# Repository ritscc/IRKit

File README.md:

# IRKit
KC3 2019 RCC勉強会
IRKit 基板設計データ
# Dependency
[KiCAD](http://kicad-pcb.org)

## FootPrint
- [ZX62-B-PA(33)](https://www.snapeda.com/parts/ZX62-B-5PA%2833%29/Hirose%20Electric%20Co%20Ltd/view-part/)
- [BS170](https://www.snapeda.com/parts/BS170/ON%20Semiconductor/view-part/)
- [kc3_logo](KiCad/lib/kc3-logo/kc3_logo.pretty)
- [AKI-PARTS](KiCad/lib/AKI-PARTS.pretty)

# Setup
1. `git clone git@github.com:ritscc/IRKit.git`
1. Log in [snapeda](https://www.snapeda.com/account/login/)
1. Download & unzip [ZX62-B-PA(33)](https://www.snapeda.com/parts/ZX62-B-5PA%2833%29/Hirose%20Electric%20Co%20Ltd/view-part/), [BS170](https://www.snapeda.com/parts/BS170/ON%20Semiconductor/view-part/) FootPront to IRKit project directory `./IRKit/`

# License
This software is released under the MIT License, see LICENSE.

# Authors
RCC
- aonori@[aonrjp](https://aonr.jp)
- nekopanda@[hirotta3a](https://twitter.com/hirotta3a)

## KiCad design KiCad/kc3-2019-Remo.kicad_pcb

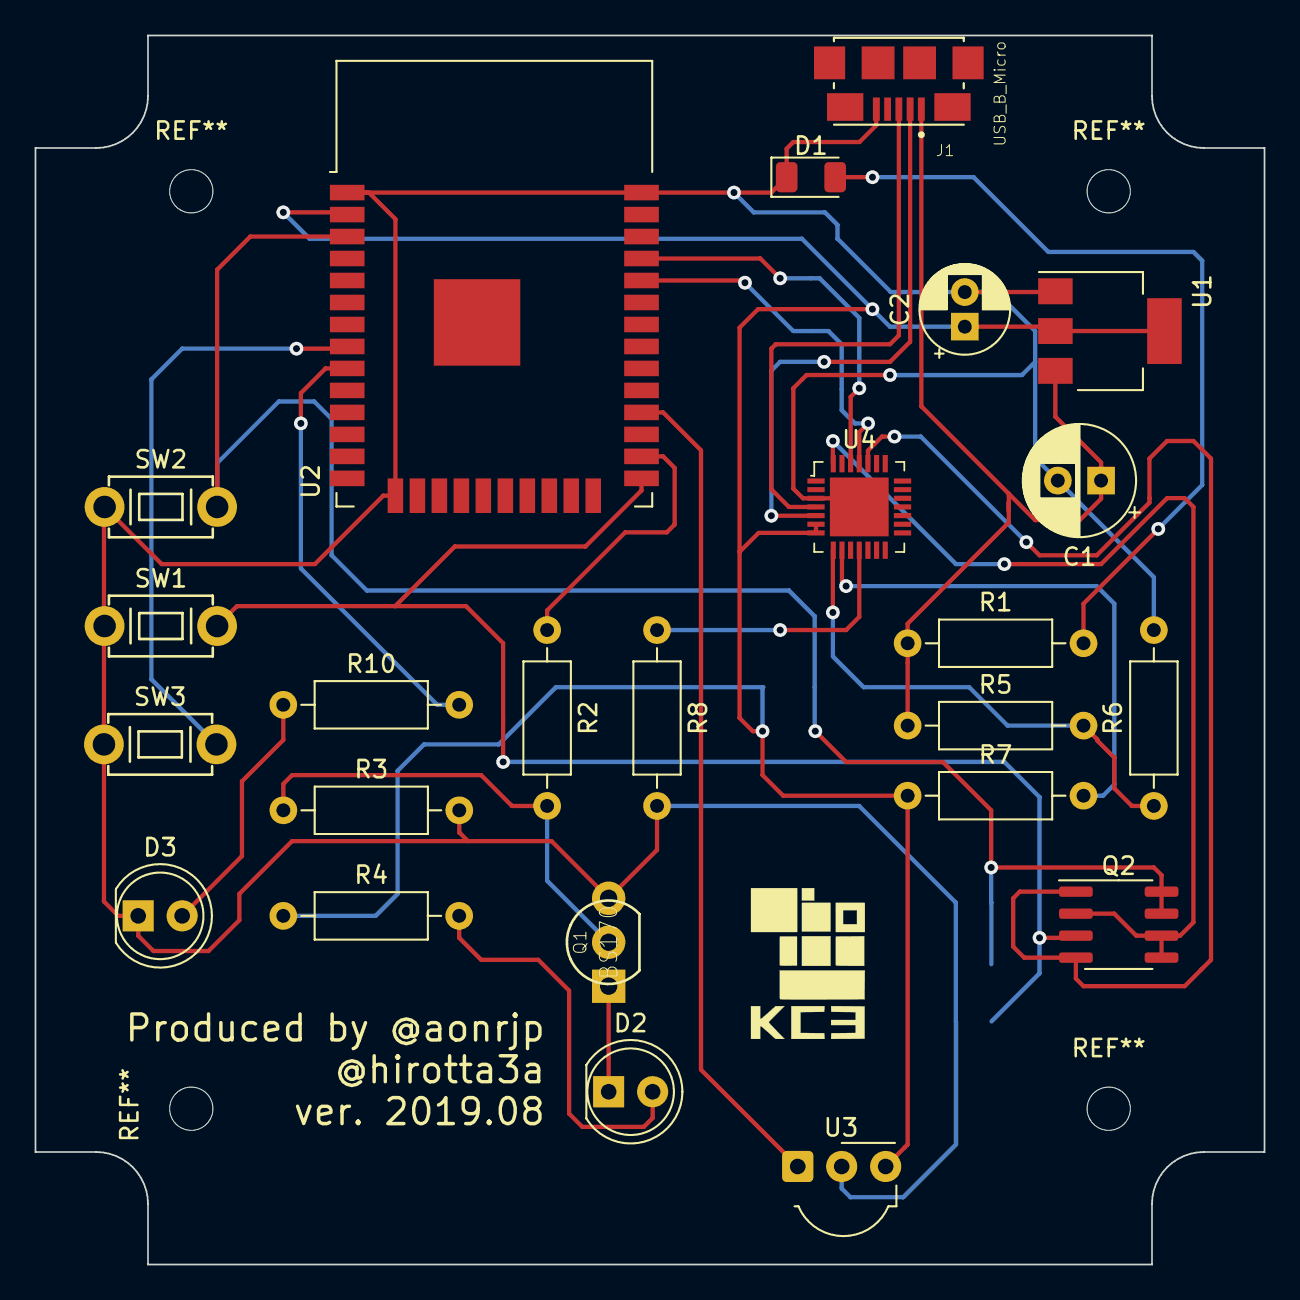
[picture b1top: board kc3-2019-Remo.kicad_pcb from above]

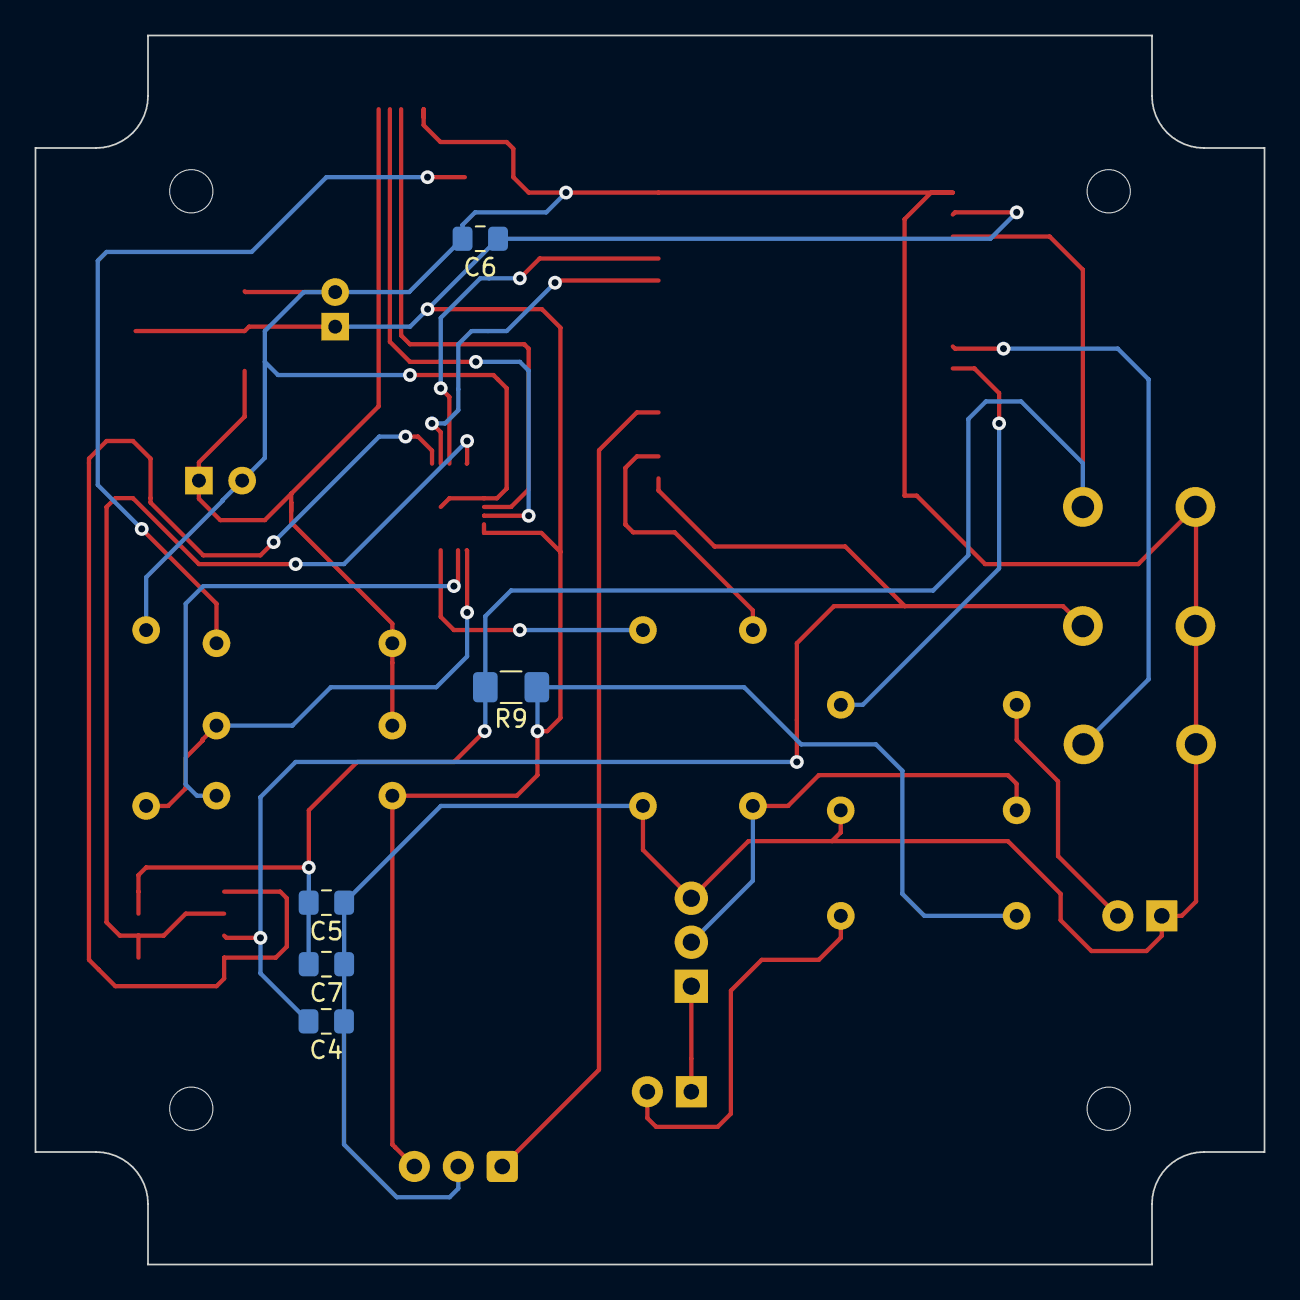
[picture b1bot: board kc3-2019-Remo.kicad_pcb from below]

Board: 2 copper layers, 71.0 x 71.0 mm, 29 parts (5 on the bottom side), 23 nets.

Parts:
C1: 47u; CP_Radial_D6.3mm_P2.50mm
C2: 22u; CP_Radial_D5.0mm_P2.00mm
C4, C5, C6, C7: 0.1u; C_0805_2012Metric_Pad1.15x1.40mm_HandSolder
D1: LED; LED_1206_3216Metric
D2: OSI5FU5111C-40; LED_D5.0mm
D3: GREEN_LED; LED_D5.0mm
J1: USB_B_Micro; HRS_ZX62-B-5PA(33)
Q1: BS170; TO92
Q2: NDS9936; SOIC-8_3.9x4.9mm_P1.27mm
R1: 2k; R_Axial_DIN0207_L6.3mm_D2.5mm_P10.16mm_Horizontal
R2, R10: 22; R_Axial_DIN0207_L6.3mm_D2.5mm_P10.16mm_Horizontal
R3, R8: 10k; R_Axial_DIN0207_L6.3mm_D2.5mm_P10.16mm_Horizontal
R4: 1; R_Axial_DIN0207_L6.3mm_D2.5mm_P10.16mm_Horizontal
R5: 24k; R_Axial_DIN0207_L6.3mm_D2.5mm_P10.16mm_Horizontal
R6: 47k; R_Axial_DIN0207_L6.3mm_D2.5mm_P10.16mm_Horizontal
R7: 4.7k; R_Axial_DIN0207_L6.3mm_D2.5mm_P10.16mm_Horizontal
R9: 10k; R_1206_3216Metric_Pad1.42x1.75mm_HandSolder
SW1: FLASH_SW; TVBP06-B043CX-B
SW2: RST_SW; TVBP06-B043CX-B
SW3: USER_SW; TVBP06-B043CX-B
U1: AMS1117-3.3; SOT-223-3_TabPin2
U2: ESP32-WROOM-32
U3: OSRB38C9AA; Vishay_MOLD-3Pin
U4: CP2102-GMR_NRND; VFQFN-28-1EP_5x5mm

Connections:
+3V3: C2.1, C6.1, R4.1, R7.1, R9.1, U1.2, U2.2, U3.3, U4.6, U4.7
+5V: C1.1, J1.1, R1.1, R5.1, U1.3
DTR: Q2.2, Q2.5, Q2.6, U4.28
EN: C5.2, C7.2, Q2.7, Q2.8, R9.2, SW2.1, U2.3
GND: C1.2, C2.2, C4.1, C5.1, C6.2, C7.1, D1.1, D3.1, J1.5, Q1.3, R3.2, R6.2, R8.2, SW1.2, SW2.2, SW3.2, U1.1, U2.1, U2.15, U2.38, U3.2, U4.3, U4.29
IO0: C4.2, Q2.3, SW1.1, U2.25
IR_LED: R2.1, U2.26
IR_REC: U2.28, U3.1
unnamed: D1.2, R1.2
unnamed: D2.1, Q1.1
unnamed: D2.2, R4.2
unnamed: D3.2, R10.1
unnamed: Q1.2, R2.2, R3.1
unnamed: R5.2, R6.1, U4.8
unnamed: R7.2, U4.9
unnamed: R8.1, U4.11
unnamed: R10.2, U2.9
unnamed: SW3.1, U2.8
RTS: Q2.1, Q2.4, U4.24
RXD0: U2.34, U4.25
TXD0: U2.35, U4.26
USB_DN: J1.2, U4.5
USB_DP: J1.3, U4.4

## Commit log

2019-09-01 edit readme
2019-09-05 Refactor parts library directories.
2019-09-05 Move KiCad project files into 'KiCad' dir.
2019-09-05 add kicad pcb file
2019-09-05 Update issue templates
2019-09-05 edit url
2019-09-05 Refactor link text on Readme file.
    * edit README
2019-09-07 Add initial Platform-IDE project for 'brd-check'.
2019-09-07 Add User_SW and Green_LED test code.
2019-09-07 Check Wi-Fi
2019-09-07 Add IRLED-RECV&SEND GREENLED
2019-09-08 Refactor programs.
